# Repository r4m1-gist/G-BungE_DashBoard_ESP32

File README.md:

# G-BungE Dashboard ESP32

This project is an ESP32-based dashboard for the final Baja vehicle, Mk.5.
It aims to display vehicle status on 4-digit 7-segment modules using CAN data from the Sevcon Gen4 Size 6 controller.

Firmware and hardware resources for the G-BungE Mk.5 Baja EV dashboard.

## Project Layout

```text
Firmware/
  main/
    main.ino

  test/
    ledsegmentcheck/
      ledsegmentcheck.ino

    soc_can_display/
      soc_can_display.ino

Hardware/
  README.md

  PCB KiCAD files/
    009_GBdashboard.kicad_pcb
    009_GBdashboard.kicad_pro
    009_GBdashboard.kicad_sch

    gerber/
      009_GBdashboard.zip
      info.md

  STEP files/
    DashBoard PLA Housing.step

  images/
    dashboard-pcb-preview.png
```

## Firmware

- `Firmware/main/main.ino`: main dashboard sketch for the Mk.5 vehicle
- `Firmware/test/ledsegmentcheck/ledsegmentcheck.ino`: basic check sketch for three 7-segment modules and CAN communication
- `Firmware/test/soc_can_display/soc_can_display.ino`: test sketch for displaying SoC, temperature, and voltage values received over CAN

## Hardware

- Controller: NodeMCU ESP32-S
- CAN transceiver: SN65HVD230
- Display: 4-digit 7-segment module x3
- PCB source: `Hardware/PCB KiCAD files/009_GBdashboard.kicad_pcb`, `Hardware/PCB KiCAD files/009_GBdashboard.kicad_sch`, `Hardware/PCB KiCAD files/009_GBdashboard.kicad_pro`
- Manufacturing export: `Hardware/PCB KiCAD files/gerber/009_GBdashboard.zip`
- 3D PLA housing: `Hardware/STEP files/DashBoard PLA Housing.step`

## Pin Map

### 7-Segment Display

| Part | SCLK | RCLK | DIO |
| --- | --- | --- | --- |
| SEG1 | GPIO21 | GPIO22 | GPIO17 |
| SEG2 | GPIO18 | GPIO19 | GPIO23 |
| SEG3 | GPIO13 | GPIO14 | GPIO25 |

### CAN

| Part | ESP32 Pin |
| --- | --- |
| CAN TXD / CTX | GPIO26 |
| CAN RXD / CRX | GPIO27 |

## CAN / Display Behavior

- CAN bus speed: 500 kbps
- Main sketch polls the Sevcon controller over CANopen SDO.
- Display 1 shows motor speed in rpm.
- Display 2 shows motor temperature in degrees Celsius.
- Test sketches are kept for segment wiring checks and CAN receive/display checks before vehicle installation.

## Notes

- Main firmware is built around the Sevcon Gen4 Size 6 controller used in the Mk.5 Baja EV.
- CAN bus termination should be 120 ohm only at each end of the bus.
- Segment display polarity can be adjusted in each sketch with `SEGMENT_ACTIVE_LOW`, `DIGIT_ACTIVE_HIGH`, and `SEND_SEGMENTS_FIRST`.
- Hardware PCB files were added under `Hardware/` for Mk.5 dashboard fabrication and reference.

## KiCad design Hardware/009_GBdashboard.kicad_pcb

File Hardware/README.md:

# Hardware

Hardware resources for the G-BungE Mk.5 ESP32 dashboard.

## PCB KiCad Files

- Source files: `PCB KiCAD files/009_GBdashboard.kicad_pcb`, `PCB KiCAD files/009_GBdashboard.kicad_sch`, `PCB KiCAD files/009_GBdashboard.kicad_pro`
- Gerber export: `PCB KiCAD files/gerber/009_GBdashboard.zip`
- Made by quserunknownp.

## STEP Files

- Dashboard PLA housing: `STEP files/DashBoard PLA Housing.step`
- Made by r4m1.

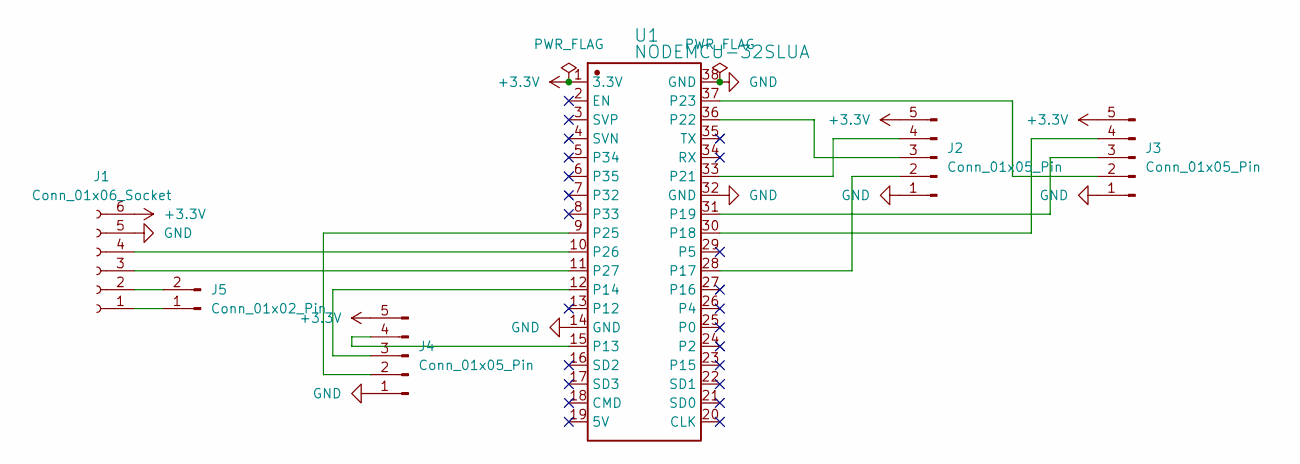
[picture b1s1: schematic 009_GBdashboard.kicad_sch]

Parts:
J1: Conn_01x06_Socket; PinHeader_1x06_P2.54mm_Vertical
J2, J3, J4: Conn_01x05_Pin; PinHeader_1x05_P2.54mm_Vertical
J5: Conn_01x02_Pin; Samtec_HPM-02-01-x-S_Straight_1x02_Pitch5.08mm
U1: NODEMCU-32SLUA; COMM-TH_NODEMCU-32SLUA; Manufacturer Part NodeMCU-32SLua

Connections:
+3.3V: J1.6, J2.5, J3.5, J4.5, U1.1 (3.3V)
GND: J1.5, J2.1, J3.1, J4.1, U1.14 (GND), U1.32 (GND), U1.38 (GND)
unnamed: J1.1, J5.1
unnamed: J1.2, J5.2
unnamed: J1.3, U1.11 (P27)
unnamed: J1.4, U1.10 (P26)
unnamed: J2.2, U1.28 (P17)
unnamed: J2.3, U1.36 (P22)
unnamed: J2.4, U1.33 (P21)
unnamed: J3.2, U1.37 (P23)
unnamed: J3.3, U1.31 (P19)
unnamed: J3.4, U1.30 (P18)
unnamed: J4.2, U1.9 (P25)
unnamed: J4.3, U1.12 (P14)
unnamed: J4.4, U1.15 (P13)

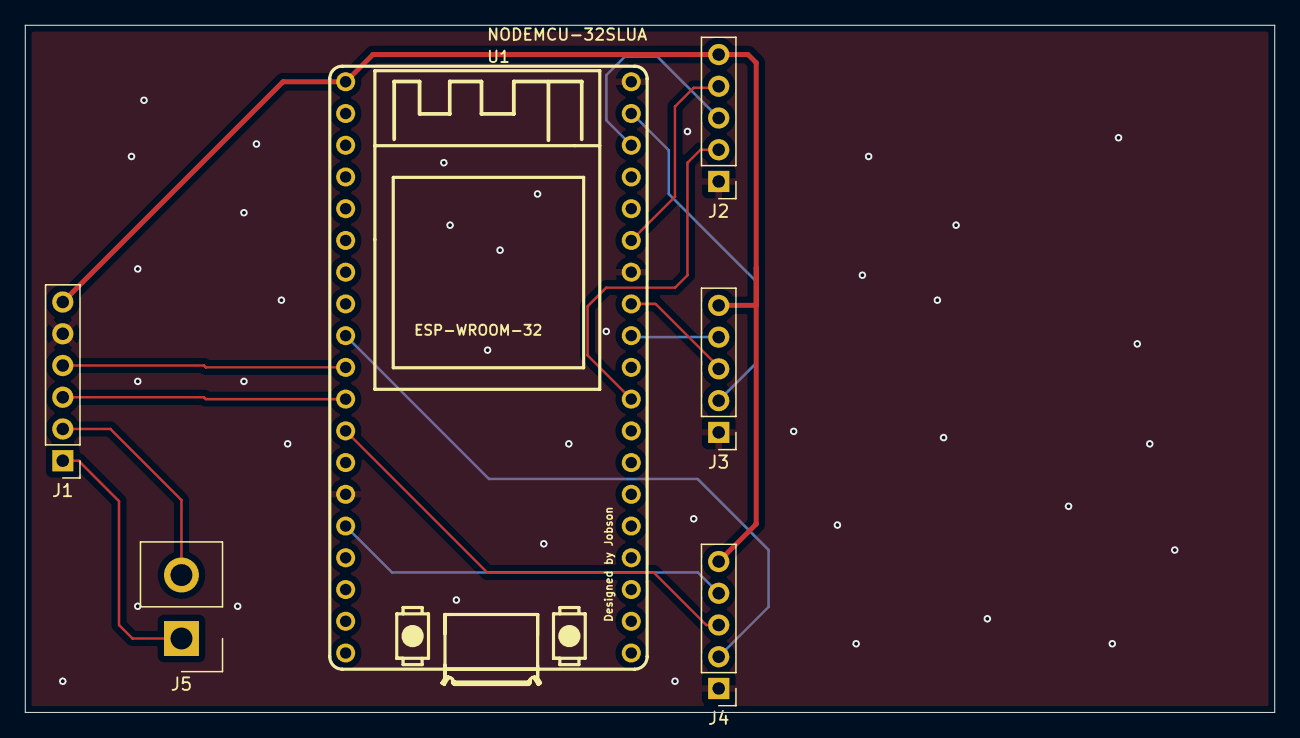
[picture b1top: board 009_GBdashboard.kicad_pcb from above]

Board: 2 copper layers, 100.0 x 55.0 mm, 6 parts (0 on the bottom side), 15 nets.

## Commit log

2026-04-22 Add .gitignore file for various build and OS files
2026-05-09 Add ESP32 segment test sketch
2026-05-10 Add greeting message to README
2026-05-10 Add greeting in Korean to README
2026-05-14 CAN test
2026-05-17 Organize Arduino dashboard sketches
2026-05-20 LED Segment Pin Change
2026-05-20 Document dashboard pin map
2026-05-20 Split firmware and hardware directories
2026-06-02 Add author information to README.md
2026-06-02 Update main README for Mk.5 dashboard hardware
2026-06-02 Refine README wording in English
2026-06-02 Final README
    Removed duplicate project title from README.
2026-06-04 Organize Fold
